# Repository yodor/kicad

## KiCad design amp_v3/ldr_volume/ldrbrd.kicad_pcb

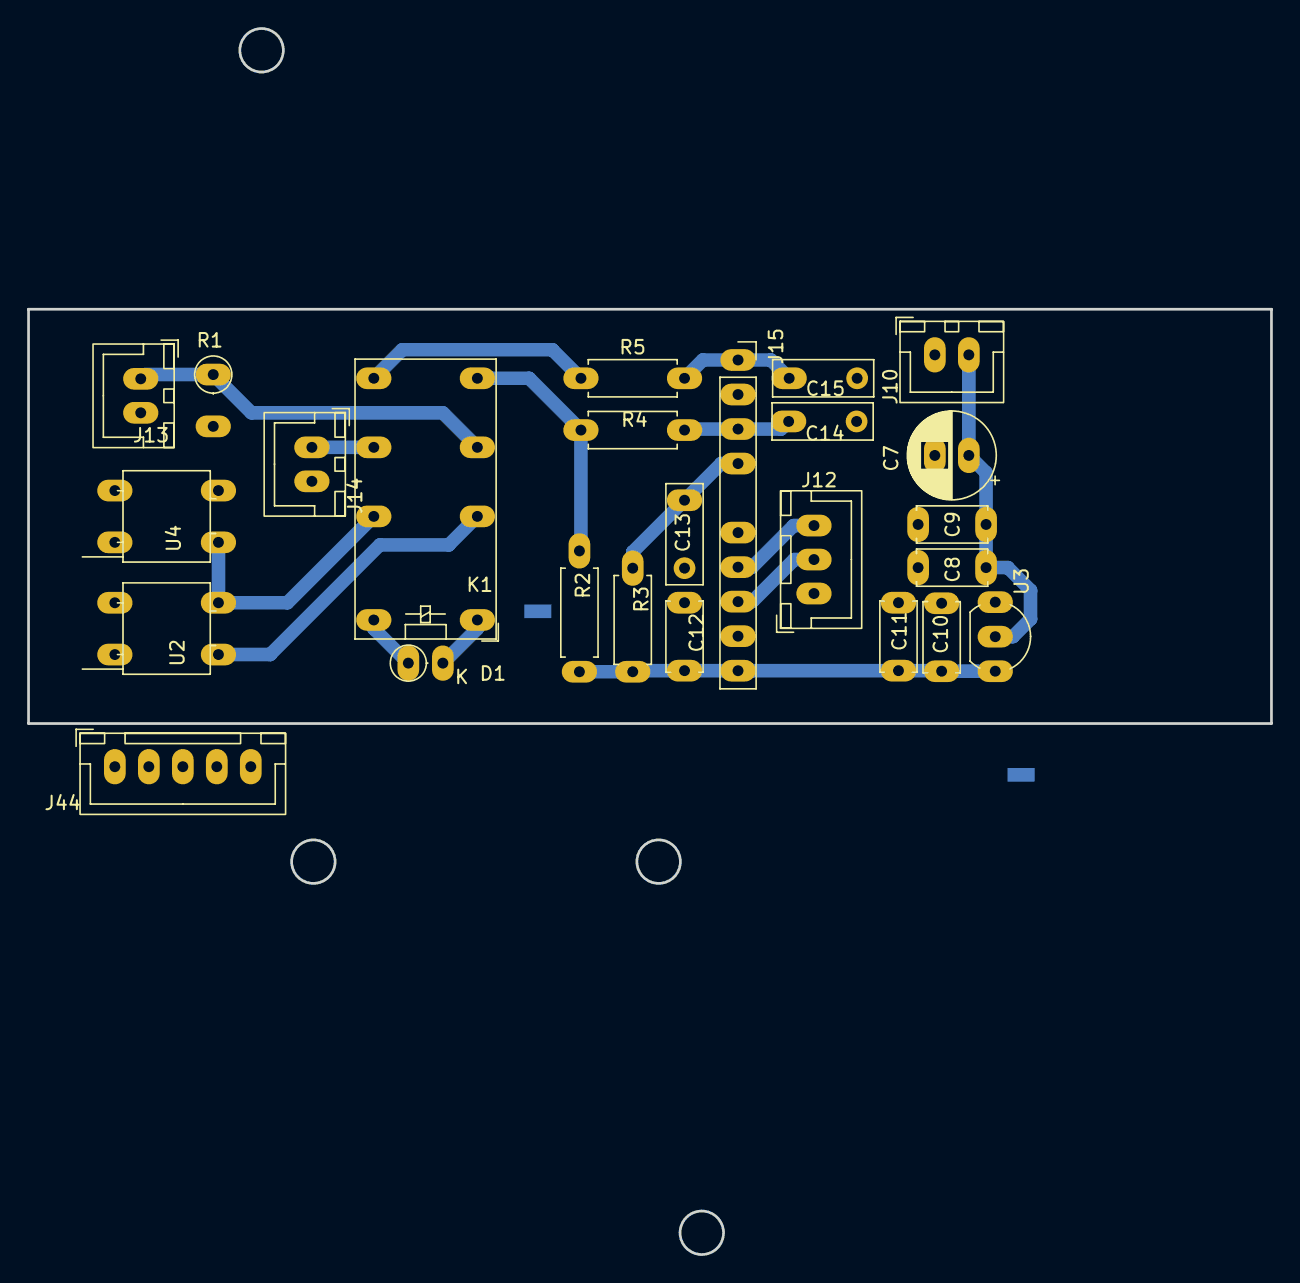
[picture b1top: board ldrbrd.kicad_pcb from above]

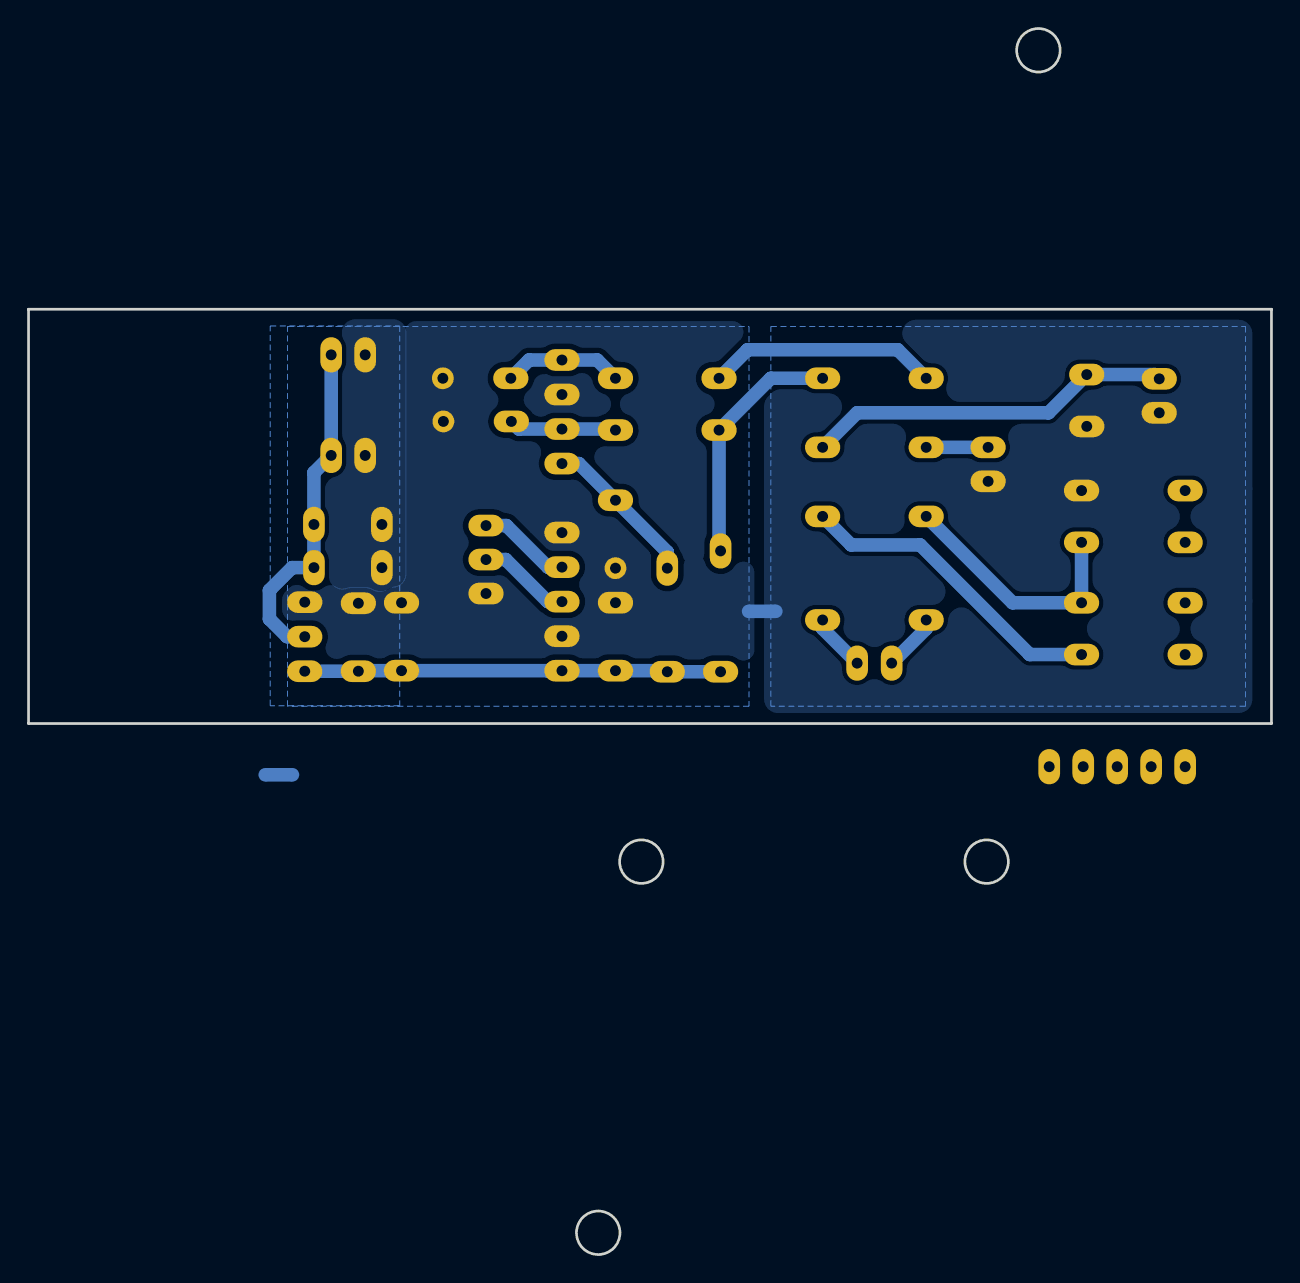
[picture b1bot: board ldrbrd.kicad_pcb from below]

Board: 2 copper layers, 91.4 x 30.5 mm, 27 parts (2 on the bottom side), 21 nets.

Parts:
C7: 100uF; CP_Radial_D6.3mm_P2.50mm
C8, C11: 1uF; C_Disc_D5.0mm_W2.5mm_P5.00mm
C9, C10, C12: 100nF; C_Disc_D5.0mm_W2.5mm_P5.00mm
C13, C14, C15: 100nF; C_Rect_L7.2mm_W2.5mm_P5.00mm_FKS2_FKP2_MKS2_MKP2
D1: 1n4007; D_DO-35_SOD27_P2.54mm_Vertical_CathodeUp
J10: 5v_in; JST_XH_B2B-XH-A_1x02_P2.50mm_Vertical
J12: I2C_R; JST_XH_B3B-XH-A_1x03_P2.50mm_Vertical
J13: A_IN; JST_XH_B2B-XH-A_1x02_P2.50mm_Vertical
J14: A_OUT; JST_XH_B2B-XH-A_1x02_P2.50mm_Vertical
J15: ADS1115; PinSocket_1x10_P2.54mm_Vertical
J44: LDR_L; JST_XH_B5B-XH-A_1x05_P2.50mm_Vertical
K1: G5V-2; Relay_DPDT_Omron_G5V-2
NT1: ATOGNDA; NetTie-2_SMD_Pad1.0o
NT2: AUDIOGND_TO_GNDA; NetTie-2_SMD_Pad1.0o
R1: 1M; R_Axial_DIN0207_L6.3mm_D2.5mm_P2.54mm_Vertical
R2: 10K; R_Axial_DIN0207_L6.3mm_D2.5mm_P7.62mm_Horizontal
R3, R4, R5: 1K; R_Axial_DIN0207_L6.3mm_D2.5mm_P7.62mm_Horizontal
U2: NSL-32-SR3-Rseries; Luna_NSL-32
U3: MCP1700x-330xxTO; TO-92_Inline_Wide
U4: NSL-32-SR3-Rshunt; Luna_NSL-32

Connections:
/LDR Board/5v_ads: C7.1, C8.1, C9.1, J10.2, U3.2 (VI)
/LDR Board/5v_local: D1.1 (K), J44.5, K1.1
/LDR Board/A0: C13.1, J15.4, R3.1
/LDR Board/A1: C14.1, J15.3, R4.1
/LDR Board/A3: C15.1, J15.1, R5.1
/LDR Board/ADS_VDD: C10.1, C11.1, C12.1, J15.10, R2.2, R3.2, U3.3 (VO)
/LDR Board/AUDIO_IN: J13.1, K1.6, R1.1
/LDR Board/AUDIO_OUT: J14.1, K1.11
/LDR Board/COIL_NEG: D1.2 (A), J44.4, K1.16
/LDR Board/MIDDLE_JUNCTION: K1.9, R5.2
/LDR Board/SCL: J12.2, J15.8
/LDR Board/SDA: J12.3, J15.7
/LDR Board/SERIAL_POS: J44.3, U2.1 (A)
/LDR Board/SHUNT_POS: J44.1, U4.1 (A)
/LDR Board/TOP_JUNCTION: K1.8, R2.1, R4.2
/LDR Board/gnd_analog: C7.2, C8.2, C9.2, J10.1, NT1.1
AUDIO_GND: J13.2, J14.2, NT2.1, R1.2, U4.3 (R)
GNDA: C10.2, C11.2, C12.2, C13.2, C14.2, C15.2, J12.1, J15.2, J15.6, J15.9, NT1.2, NT2.2, U3.1 (GND)
GNDD: J44.2, U2.2 (K), U4.2 (K)
unnamed: K1.4, U2.4 (R)
unnamed: K1.13, U2.3 (R), U4.4 (R)

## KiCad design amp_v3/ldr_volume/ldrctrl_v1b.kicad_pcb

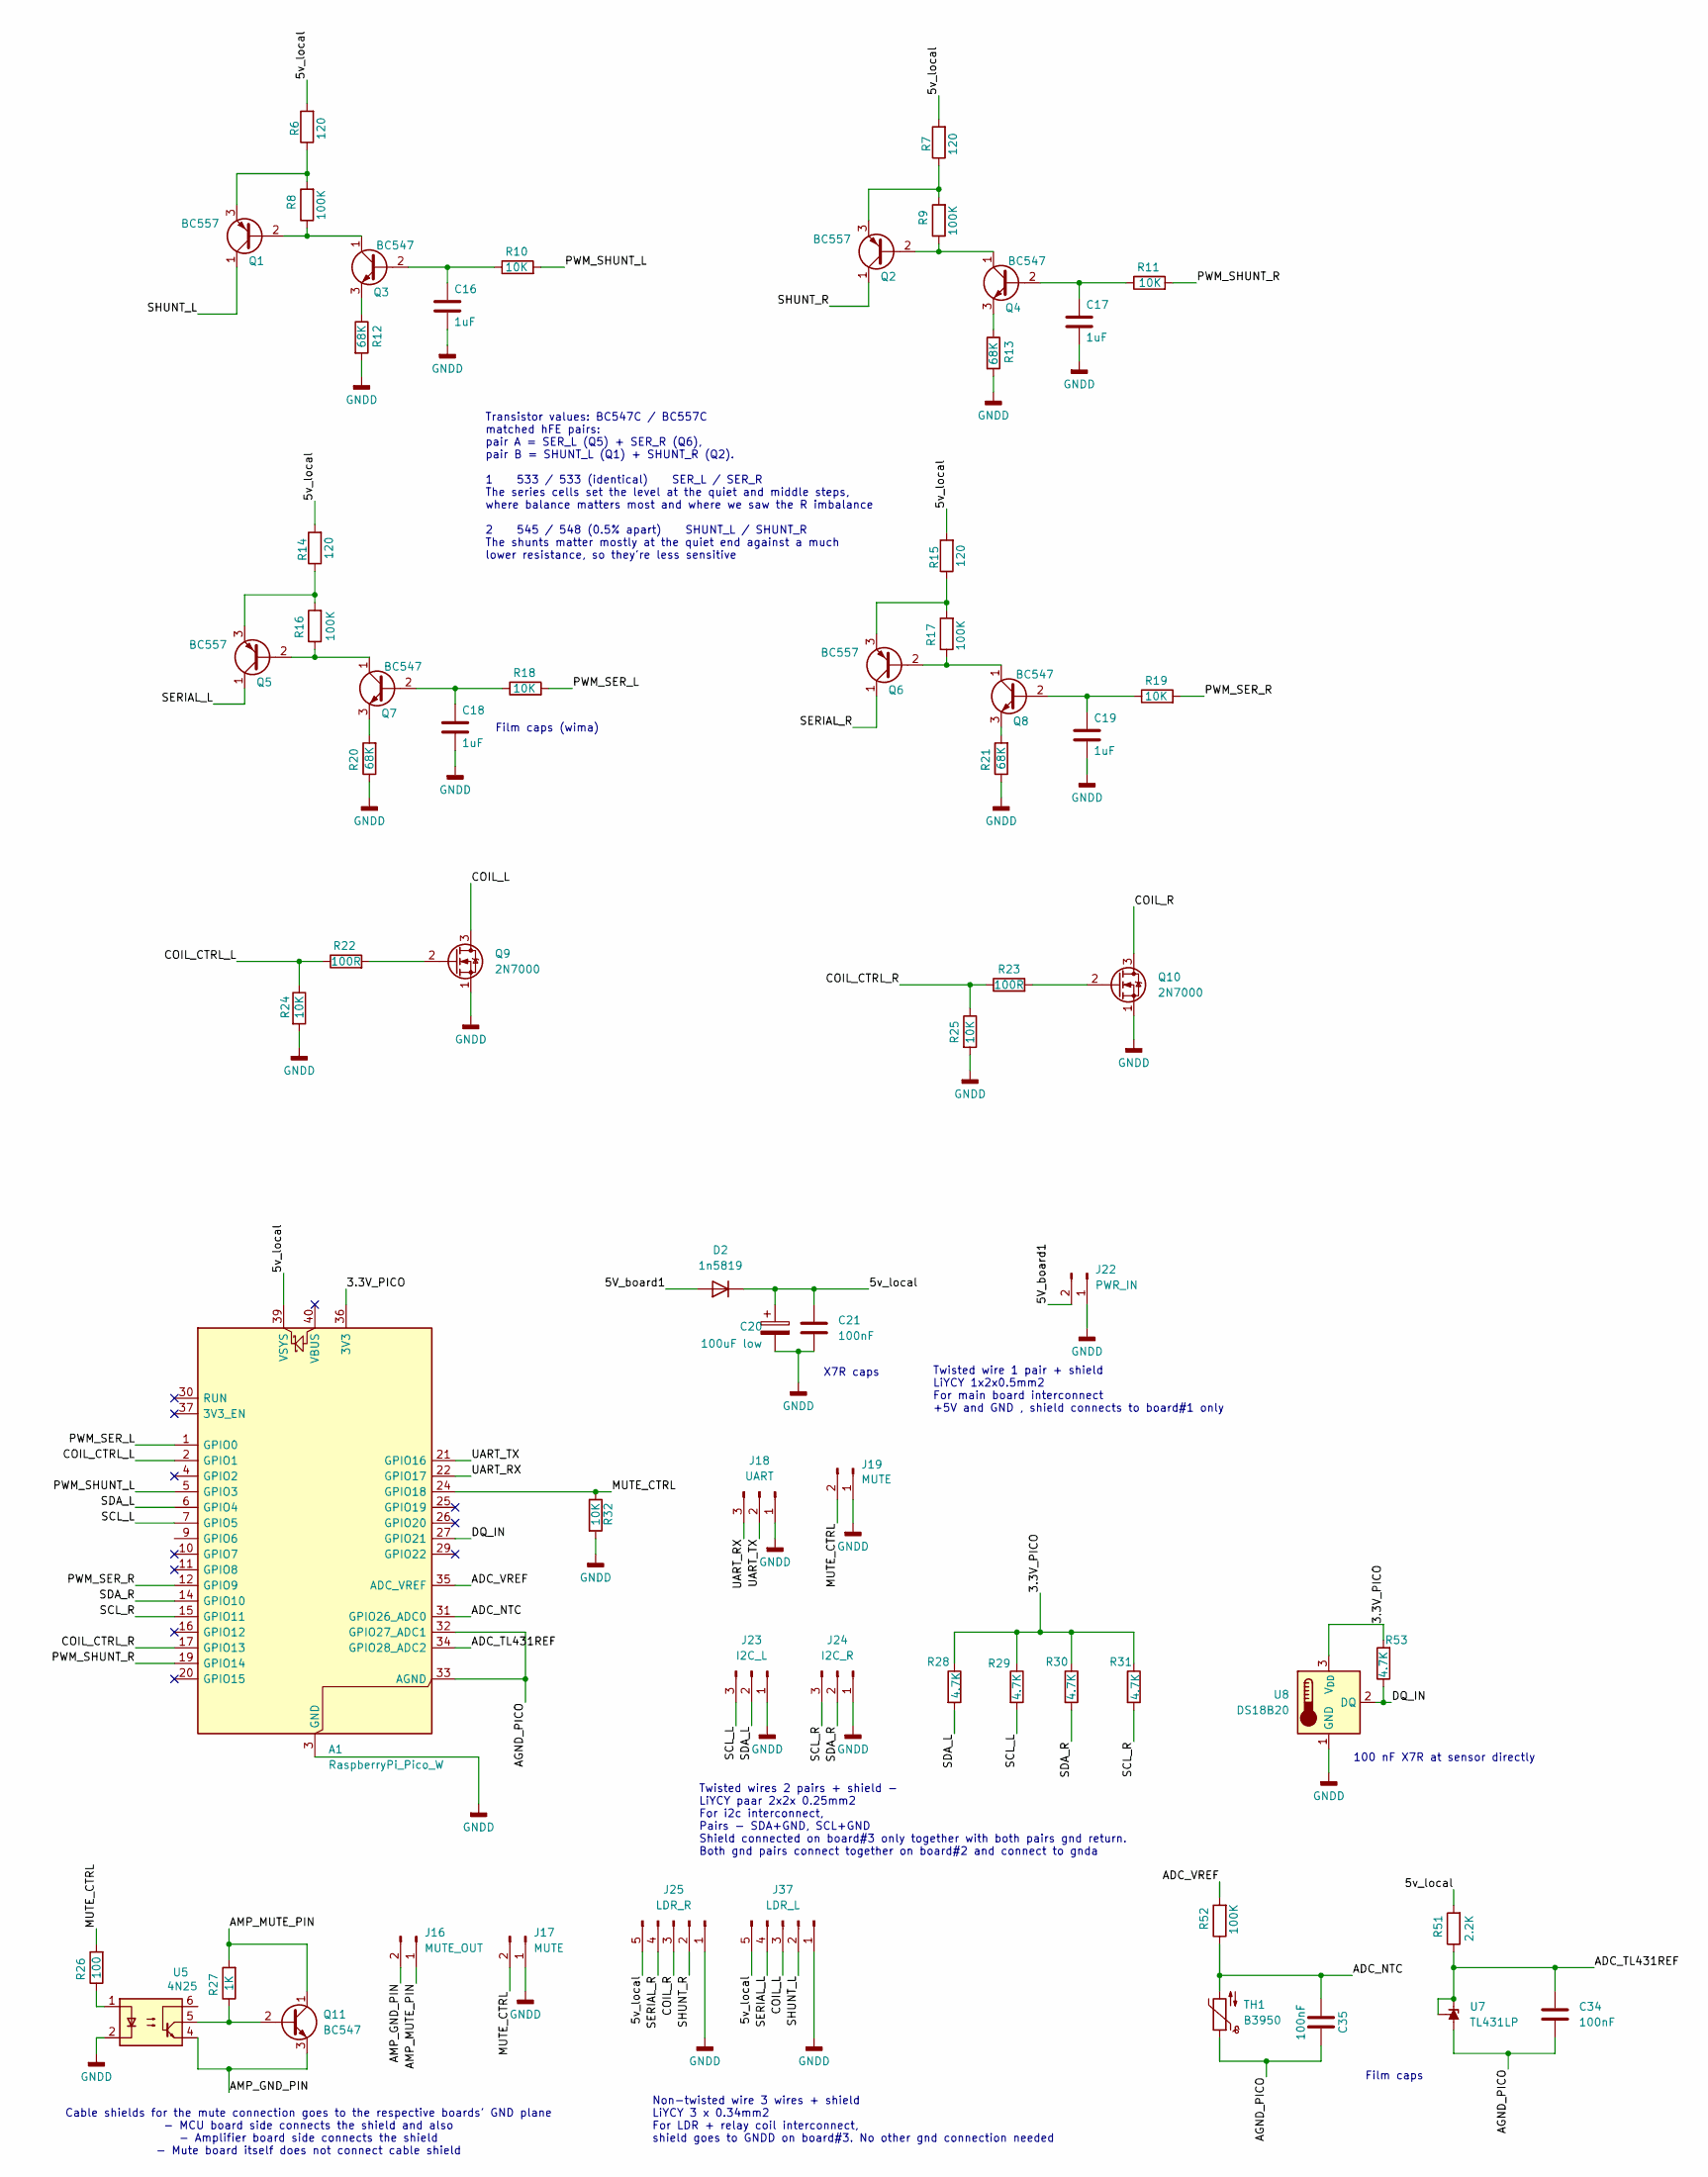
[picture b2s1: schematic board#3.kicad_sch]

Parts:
A1: RaspberryPi_Pico_W; RaspberryPi_Pico_Common_THT
C16, C17, C18, C19: 1uF; C_Rect_L7.2mm_W4.5mm_P5.00mm_FKS2_FKP2_MKS2_MKP2
C20: 100uF low; CP_Radial_D6.3mm_P2.50mm
C21, C34, C35: 100nF; C_Disc_D5.0mm_W2.5mm_P5.00mm
D2: 1n5819; D_DO-41_SOD81_P3.81mm_Vertical_CathodeUp
J16: MUTE_OUT; JST_XH_B2B-XH-A_1x02_P2.50mm_Vertical
J17, J19: MUTE; JST_XH_B2B-XH-A_1x02_P2.50mm_Vertical
J18: UART; JST_XH_B3B-XH-A_1x03_P2.50mm_Vertical
J22: PWR_IN; JST_XH_B2B-XH-A_1x02_P2.50mm_Vertical
J23: I2C_L; JST_XH_B3B-XH-A_1x03_P2.50mm_Vertical
J24: I2C_R; JST_XH_B3B-XH-A_1x03_P2.50mm_Vertical
J25: LDR_R; JST_XH_B5B-XH-A_1x05_P2.50mm_Vertical
J37: LDR_L; JST_XH_B5B-XH-A_1x05_P2.50mm_Vertical
Q1, Q2, Q5, Q6: BC557; TO-92_Inline_Wide
Q3, Q4, Q7, Q8, Q11: BC547; TO-92_Inline_Wide
Q9, Q10: 2N7000; TO-92_Inline_Wide
R6, R7: 120; R_Axial_DIN0207_L6.3mm_D2.5mm_P7.62mm_Horizontal
R8, R9, R16, R17, R52: 100K; R_Axial_DIN0207_L6.3mm_D2.5mm_P7.62mm_Horizontal
R10, R11, R18, R19, R24, R25, R32: 10K; R_Axial_DIN0207_L6.3mm_D2.5mm_P7.62mm_Horizontal
R12, R13, R20, R21: 68K; R_Axial_DIN0207_L6.3mm_D2.5mm_P7.62mm_Horizontal
R14, R15: 120; R_Axial_DIN0207_L6.3mm_D2.5mm_P2.54mm_Vertical
R22, R23: 100R; R_Axial_DIN0207_L6.3mm_D2.5mm_P7.62mm_Horizontal
R26: 100; R_Axial_DIN0207_L6.3mm_D2.5mm_P7.62mm_Horizontal
R27: 1K; R_Axial_DIN0207_L6.3mm_D2.5mm_P7.62mm_Horizontal
R28, R29, R30, R31: 4.7K; R_Axial_DIN0207_L6.3mm_D2.5mm_P7.62mm_Horizontal
R51: 2.2K; R_Axial_DIN0207_L6.3mm_D2.5mm_P7.62mm_Horizontal
R53: 4.7K; R_Axial_DIN0207_L6.3mm_D2.5mm_P2.54mm_Vertical
TH1: B3950; JST_XH_B2B-XH-A_1x02_P2.50mm_Vertical
U5: 4N25; DIP-6_W7.62mm
U7: TL431LP; TO-92_Inline_Wide
U8: DS18B20; JST_XH_B3B-XH-A_1x03_P2.50mm_Vertical

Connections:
/LDR Driver/3.3V_PICO: A1.36 (3V3), R28.1, R29.1, R30.1, R31.1, R53.2, U8.3 (V_{DD})
/LDR Driver/5V_board1: D2.2 (A), J22.2
/LDR Driver/5v_local: A1.39 (VSYS), C20.1, C21.1, D2.1 (K), J25.5, J37.5, R6.2, R7.2, R14.2, R15.2, R51.2
/LDR Driver/ADC_NTC: A1.31 (GPIO26_ADC0), C35.1, R52.1, TH1.2
/LDR Driver/ADC_TL431REF: A1.34 (GPIO28_ADC2), C34.1, R51.1, U7.1 (REF), U7.3 (K)
/LDR Driver/ADC_VREF: A1.35 (ADC_VREF), R52.2
/LDR Driver/AGND_PICO: A1.32 (GPIO27_ADC1), A1.33 (AGND), C34.2, C35.2, TH1.1, U7.2 (A)
/LDR Driver/AMP_GND_PIN: J16.2, Q11.3 (E), U5.4
/LDR Driver/AMP_MUTE_PIN: J16.1, Q11.1 (C), R27.2
/LDR Driver/COIL_CTRL_L: A1.2 (GPIO1), R22.1, R24.1
/LDR Driver/COIL_CTRL_R: A1.17 (GPIO13), R23.1, R25.1
/LDR Driver/COIL_L: J37.3, Q9.3 (D)
/LDR Driver/COIL_R: J25.3, Q10.3 (D)
/LDR Driver/DQ_IN: A1.27 (GPIO21), R53.1, U8.2 (DQ)
/LDR Driver/MUTE_CTRL: A1.24 (GPIO18), J17.2, J19.2, R26.2, R32.1
/LDR Driver/PWM_SER_L: A1.1 (GPIO0), R18.2
/LDR Driver/PWM_SER_R: A1.12 (GPIO9), R19.2
/LDR Driver/PWM_SHUNT_L: A1.5 (GPIO3), R10.2
/LDR Driver/PWM_SHUNT_R: A1.19 (GPIO14), R11.2
/LDR Driver/SCL_L: A1.7 (GPIO5), J23.3, R29.2
/LDR Driver/SCL_R: A1.15 (GPIO11), J24.3, R31.2
/LDR Driver/SDA_L: A1.6 (GPIO4), J23.2, R28.2
/LDR Driver/SDA_R: A1.14 (GPIO10), J24.2, R30.2
/LDR Driver/SERIAL_L: J37.4, Q5.1 (C)
/LDR Driver/SERIAL_R: J25.4, Q6.1 (C)
/LDR Driver/SHUNT_L: J37.2, Q1.1 (C)
/LDR Driver/SHUNT_R: J25.2, Q2.1 (C)
/LDR Driver/UART_RX: A1.22 (GPIO17), J18.3
/LDR Driver/UART_TX: A1.21 (GPIO16), J18.2
GNDD: A1.3 (GND), A1.8 (GND), A1.13 (GND), A1.18 (GND), A1.23 (GND), A1.28 (GND), A1.38 (GND), C16.2, C17.2, C18.2, C19.2, C20.2, C21.2, J17.1, J18.1, J19.1, J22.1, J23.1, J24.1, J25.1, J37.1, Q9.1 (S), Q10.1 (S), R12.2, R13.2, R20.1, R21.1, R24.2, R25.2, R32.2, U5.2, U8.1 (GND)
unnamed: Q1.2 (B), Q3.1 (C), R8.1
unnamed: Q1.3 (E), R6.1, R8.2
unnamed: Q2.2 (B), Q4.1 (C), R9.1
unnamed: Q2.3 (E), R7.1, R9.2
unnamed: C16.1, Q3.2 (B), R10.1
unnamed: Q3.3 (E), R12.1
unnamed: C17.1, Q4.2 (B), R11.1
unnamed: Q4.3 (E), R13.1
unnamed: Q5.2 (B), Q7.1 (C), R16.1
unnamed: Q5.3 (E), R14.1, R16.2
unnamed: Q6.2 (B), Q8.1 (C), R17.1
unnamed: Q6.3 (E), R15.1, R17.2
unnamed: C18.1, Q7.2 (B), R18.1
unnamed: Q7.3 (E), R20.2
unnamed: C19.1, Q8.2 (B), R19.1
unnamed: Q8.3 (E), R21.2
unnamed: Q9.2 (G), R22.2
unnamed: Q10.2 (G), R23.2
unnamed: Q11.2 (B), R27.1, U5.5
unnamed: R26.1, U5.1

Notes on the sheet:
100 nF X7R at sensor directly
Twisted wire 1 pair + shield LiYCY 1x2x0.5mm2 For main board interconnect +5V and GND , shield connects to board#1 only
X7R caps
Film caps
Cable shields for the mute connection goes to the respective boards' GND plane - MCU board side connects the shield and also - Amplifier board side connects the shield - Mute board itself does not connect cable shield
Twisted wires 2 pairs + shield - LiYCY paar 2x2x 0.25mm2 For i2c interconnect, Pairs - SDA+GND, SCL+GND Shield connected on board#3 only together with both pairs gnd return. Both gnd pairs connect together on board#2 and connect to gnda
Transistor values: BC547C / BC557C matched hFE pairs: pair A = SER_L (Q5) + SER_R (Q6), pair B = SHUNT_L (Q1) + SHUNT_R (Q2). 1 533 / 533 (identical) SER_L / SER_R The series cells set the level at the quiet and middle steps, where balance matters most and where we saw the R imbalance 2 545 / 548 (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
Film caps (wima)
Non-twisted wire 3 wires + shield LiYCY 3 x 0.34mm2 For LDR + relay coil interconnect, shield goes to GNDD on board#3. No other gnd connection needed

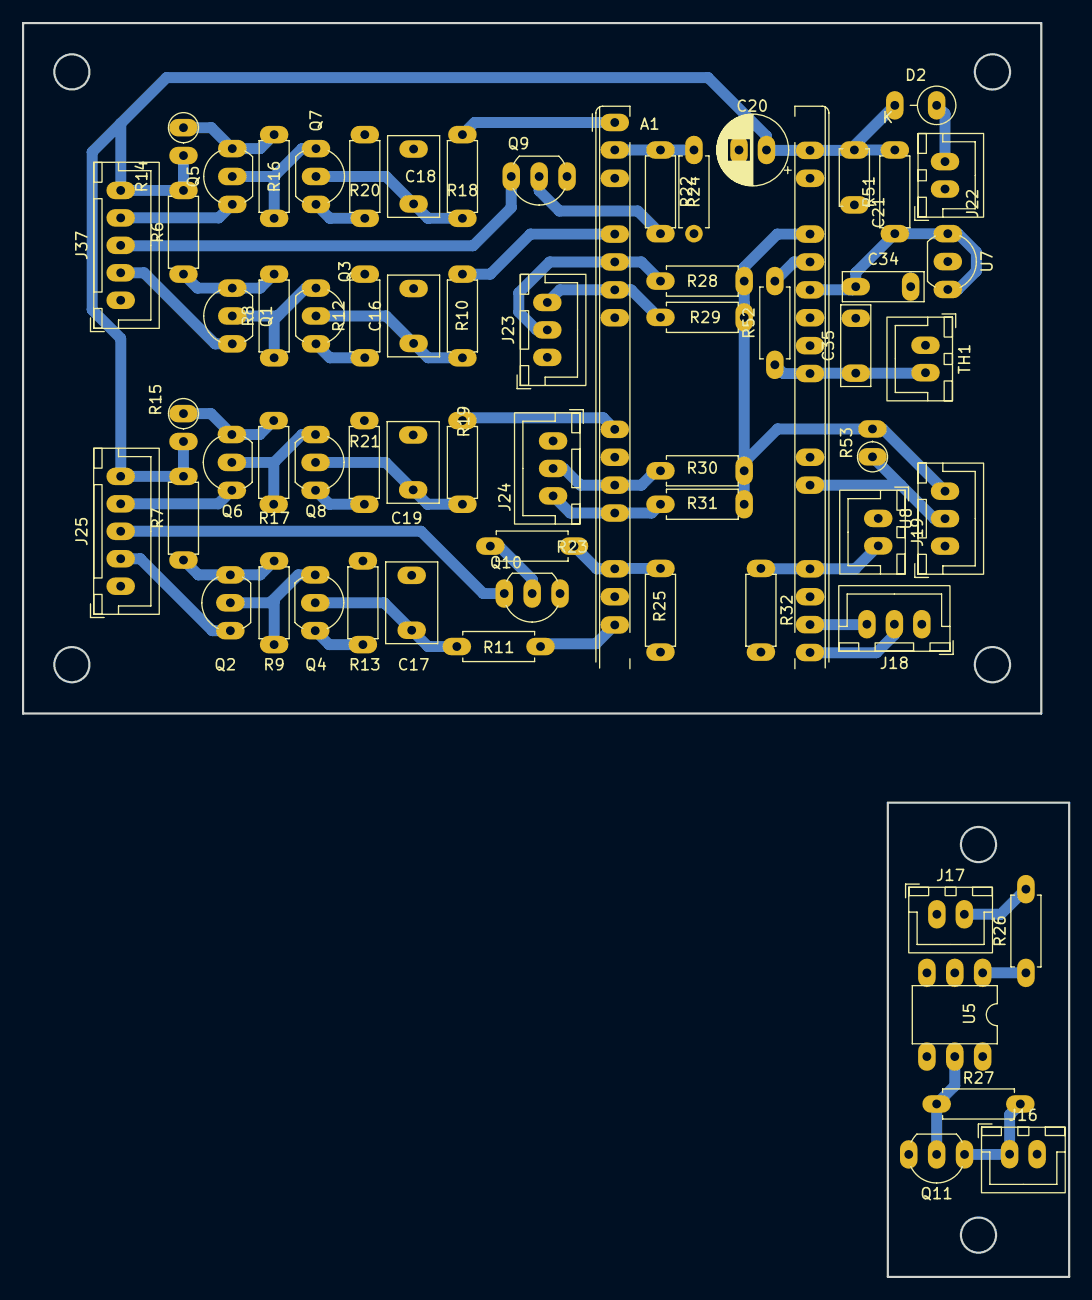
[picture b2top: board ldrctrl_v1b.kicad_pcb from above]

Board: 2 copper layers, 92.7 x 62.9 mm, 64 parts (0 on the bottom side), 50 nets.

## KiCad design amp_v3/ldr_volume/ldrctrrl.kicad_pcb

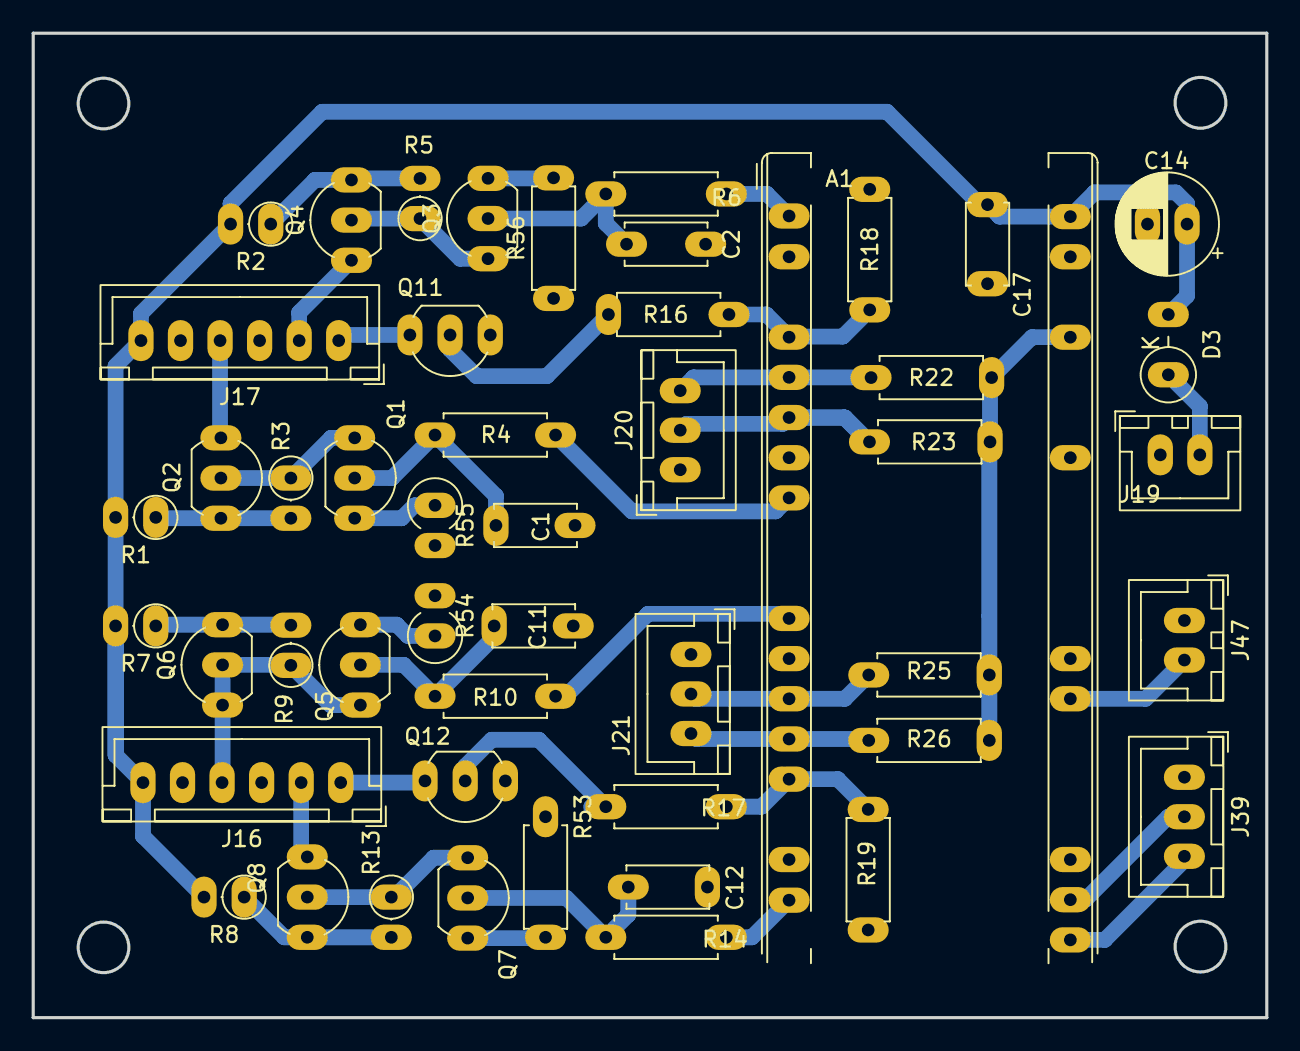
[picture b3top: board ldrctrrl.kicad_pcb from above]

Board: 2 copper layers, 78.0 x 62.2 mm, 49 parts (0 on the bottom side), 41 nets.

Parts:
A1: RaspberryPi_Pico_W; RaspberryPi_Pico_Common_THT
C1, C2, C11, C12: 10nF; C_Disc_D5.0mm_W2.5mm_P5.00mm
C14: 100uF low; CP_Radial_D6.3mm_P2.50mm
C17: 100nF; C_Disc_D5.0mm_W2.5mm_P5.00mm
D3: 1n5819; D_DO-41_SOD81_P3.81mm_Vertical_CathodeUp
J16, J17: CTRL; JST_XH_B6B-XH-A_1x06_P2.50mm_Vertical
J19: PWR_IN; JST_XH_B2B-XH-A_1x02_P2.50mm_Vertical
J20: I2C_L; JST_XH_B3B-XH-A_1x03_P2.50mm_Vertical
J21: I2C_R; JST_XH_B3B-XH-A_1x03_P2.50mm_Vertical
J39: UART; JST_XH_B3B-XH-A_1x03_P2.50mm_Vertical
J47: MUTE; JST_XH_B2B-XH-A_1x02_P2.50mm_Vertical
Q1, Q3, Q5, Q7: BC547; TO-92_Inline_Wide
Q2, Q4, Q6, Q8: BC557; TO-92_Inline_Wide
Q11, Q12: 2N7000; TO-92_Inline_Wide
R1, R2, R7, R8: 120; R_Axial_DIN0207_L6.3mm_D2.5mm_P2.54mm_Vertical
R3, R5, R9, R13: 100K; R_Axial_DIN0207_L6.3mm_D2.5mm_P2.54mm_Vertical
R4, R6, R10, R14, R18, R19: 10K; R_Axial_DIN0207_L6.3mm_D2.5mm_P7.62mm_Horizontal
R16, R17: 100R; R_Axial_DIN0207_L6.3mm_D2.5mm_P7.62mm_Horizontal
R22, R23, R25, R26: 4.7K; R_Axial_DIN0207_L6.3mm_D2.5mm_P7.62mm_Horizontal
R53, R56: 68K; R_Axial_DIN0207_L6.3mm_D2.5mm_P7.62mm_Horizontal
R54, R55: 68K; R_Axial_DIN0309_L9.0mm_D3.2mm_P2.54mm_Vertical

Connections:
/LDR Driver/3.3V_PICO: A1.36 (3V3), R22.1, R23.1, R25.1, R26.1
/LDR Driver/5V_board1: D3.2 (A), J19.2
/LDR Driver/5v_local: A1.39 (VSYS), C14.1, C17.1, D3.1 (K), J16.6, J17.6, R1.2, R2.2, R7.2, R8.2
/LDR Driver/COIL_CTRL_L: A1.5 (GPIO3), R16.1, R18.1
/LDR Driver/COIL_CTRL_R: A1.16 (GPIO12), R17.1, R19.1
/LDR Driver/COIL_L: J17.1, Q11.3 (D)
/LDR Driver/COIL_R: J16.1, Q12.3 (D)
/LDR Driver/MUTE_CTRL: A1.27 (GPIO21), J47.2
/LDR Driver/PWM_SER_L: A1.2 (GPIO1), R6.2
/LDR Driver/PWM_SER_R: A1.19 (GPIO14), R14.2
/LDR Driver/PWM_SHUNT_L: A1.9 (GPIO6), R4.2
/LDR Driver/PWM_SHUNT_R: A1.12 (GPIO9), R10.2
/LDR Driver/SCL_L: A1.7 (GPIO5), J20.2, R23.2
/LDR Driver/SCL_R: A1.15 (GPIO11), J21.3, R26.2
/LDR Driver/SDA_L: A1.6 (GPIO4), J20.3, R22.2
/LDR Driver/SDA_R: A1.14 (GPIO10), J21.2, R25.2
/LDR Driver/SERIAL_L: J17.2, Q4.1 (C)
/LDR Driver/SERIAL_R: J16.2, Q8.1 (C)
/LDR Driver/SHUNT_L: J17.4, Q2.1 (C)
/LDR Driver/SHUNT_R: J16.4, Q6.1 (C)
/LDR Driver/UART_RX: A1.21 (GPIO16), J39.3
/LDR Driver/UART_TX: A1.22 (GPIO17), J39.2
GNDD: A1.3 (GND), A1.8 (GND), A1.13 (GND), A1.18 (GND), A1.23 (GND), A1.28 (GND), A1.33 (AGND), A1.38 (GND), C1.2, C2.2, C11.2, C12.2, C14.2, C17.2, J16.3, J16.5, J17.3, J17.5, J19.1, J20.1, J21.1, J39.1, J47.1, Q11.1 (S), Q12.1 (S), R18.2, R19.2, R53.1, R54.2, R55.2, R56.1
unnamed: C1.1, Q1.2 (B), R4.1
unnamed: Q1.1 (C), Q2.2 (B), R3.1
unnamed: Q1.3 (E), R55.1
unnamed: Q2.3 (E), R1.1, R3.2
unnamed: C2.1, Q3.2 (B), R6.1
unnamed: Q3.1 (C), Q4.2 (B), R5.1
unnamed: Q3.3 (E), R56.2
unnamed: Q4.3 (E), R2.1, R5.2
unnamed: C11.1, Q5.2 (B), R10.1
unnamed: Q5.1 (C), Q6.2 (B), R9.1
unnamed: Q5.3 (E), R54.1
unnamed: Q6.3 (E), R7.1, R9.2
unnamed: C12.1, Q7.2 (B), R14.1
unnamed: Q7.1 (C), Q8.2 (B), R13.1
unnamed: Q7.3 (E), R53.2
unnamed: Q8.3 (E), R8.1, R13.2
unnamed: Q11.2 (G), R16.2
unnamed: Q12.2 (G), R17.2

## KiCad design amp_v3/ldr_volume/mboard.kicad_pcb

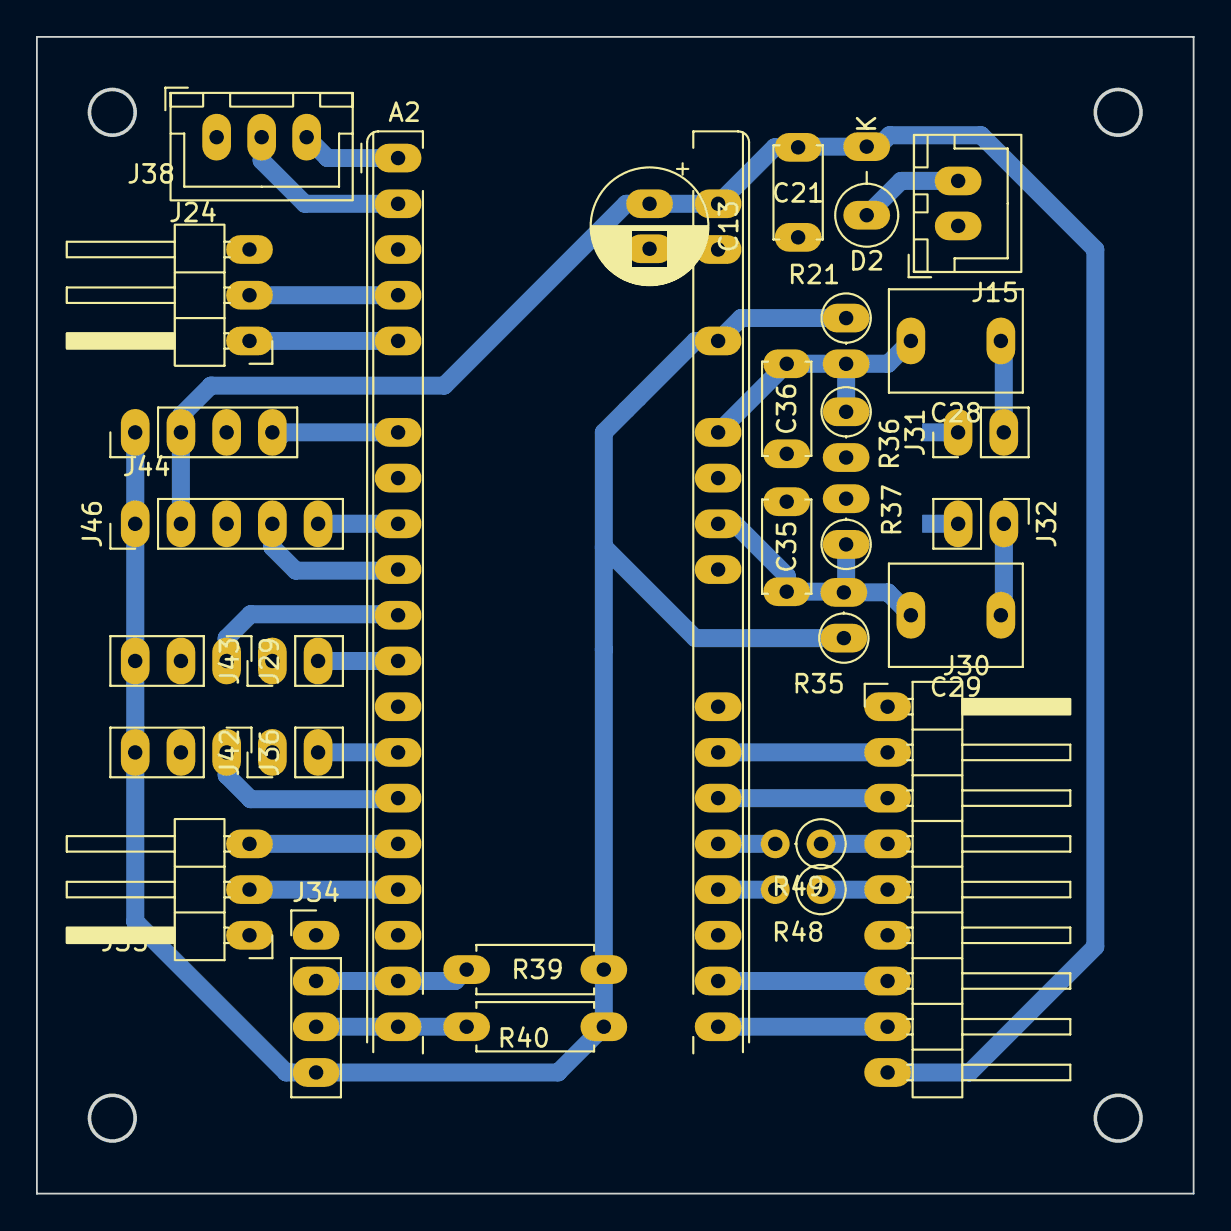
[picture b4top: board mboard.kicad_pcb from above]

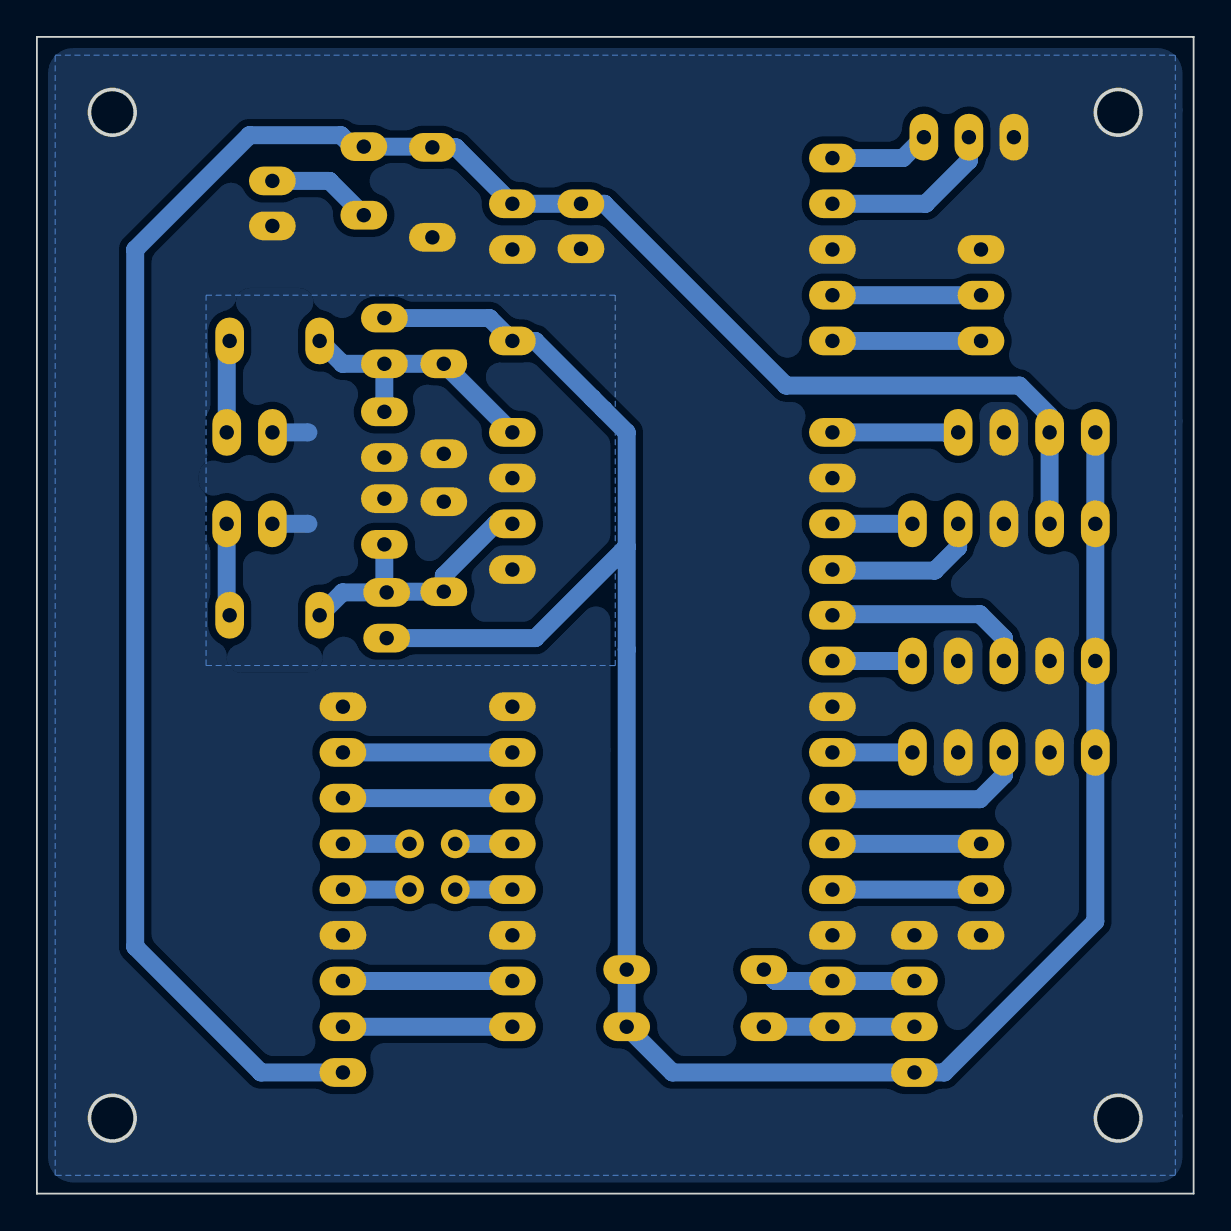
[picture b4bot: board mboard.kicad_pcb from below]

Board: 2 copper layers, 64.3 x 64.3 mm, 32 parts (2 on the bottom side), 34 nets.

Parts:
A2: RaspberryPi_Pico_W; RaspberryPi_Pico_Common_THT
C13: 100uF low; CP_Radial_D6.3mm_P2.50mm
C21: 100nF; C_Disc_D5.0mm_W2.5mm_P5.00mm
C28, C29: 1uF; C_Rect_L7.2mm_W5.5mm_P5.00mm_FKS2_FKP2_MKS2_MKP2
C35, C36: 10nF; C_Disc_D5.0mm_W2.5mm_P5.00mm
D2: 1n5817; D_DO-41_SOD81_P3.81mm_Vertical_CathodeUp
J15: PWR_IN; JST_XH_B2B-XH-A_1x02_P2.50mm_Vertical
J24: UART; JST_XH_B3B-XH-A_1x03_P2.50mm_Vertical
J29: IR; PinHeader_1x03_P2.54mm_Vertical
J30: TFT; PinHeader_1x09_P2.54mm_Horizontal
J31: S_AIN_L; PinHeader_1x02_P2.54mm_Vertical
J32: S_AIN_R; PinHeader_1x02_P2.54mm_Vertical
J34: I2C; PinHeader_1x04_P2.54mm_Vertical
J35: BTN_VOL; PinHeader_1x03_P2.54mm_Horizontal
J36: MUTE; PinHeader_1x03_P2.54mm_Vertical
J38: BTN_MENU; PinHeader_1x03_P2.54mm_Horizontal
J42: PWR_BTN; PinHeader_1x02_P2.54mm_Vertical
J43: PWR_BTN_LED; PinHeader_1x02_P2.54mm_Vertical
J44: PWR_RLY; PinHeader_1x04_P2.54mm_Vertical
J46: ALPS; PinHeader_1x05_P2.54mm_Vertical
NT7, NT8: NetTie_2; NetTie-2_SMD_Pad1.0o
R21, R35, R36, R37: 10K; R_Axial_DIN0207_L6.3mm_D2.5mm_P2.54mm_Vertical
R39, R40: 4.7K; R_Axial_DIN0207_L6.3mm_D2.5mm_P7.62mm_Horizontal
R48, R49: 22; R_Axial_DIN0207_L6.3mm_D2.5mm_P2.54mm_Vertical

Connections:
/board#5/3.3V_PICO: A2.36 (3V3), J29.3, J34.4, J36.3, J44.1, J46.1, R21.1, R35.1, R39.1, R40.1
/board#5/5V_board1: D2.2 (A), J15.2
/board#5/5v_local: A2.39 (VSYS), C13.1, C21.1, D2.1 (K), J30.9, J44.2, J46.2
/board#5/ADC_L: A2.34 (GPIO28_ADC2), C28.2, C36.1, R21.2, R36.1
/board#5/ADC_R: A2.32 (GPIO27_ADC1), C29.2, C35.2, R35.2, R37.1
/board#5/AGND_L: J31.1, NT8.1
/board#5/AGND_PICO: A2.31 (GPIO26_ADC0), A2.33 (AGND), C35.1, C36.2, NT7.2, NT8.2, R36.2, R37.2
/board#5/AGND_R: J32.2, NT7.1
/board#5/ALPS_L: A2.10 (GPIO7), J46.4
/board#5/ALPS_R: A2.9 (GPIO6), J46.5
/board#5/AUDIO_L: C28.1, J31.2
/board#5/AUDIO_R: C29.1, J32.1
/board#5/BTN_DN: A2.17 (GPIO13), J35.2
/board#5/BTN_LT: A2.16 (GPIO12), J35.3
/board#5/BTN_RT: A2.5 (GPIO3), J38.1
/board#5/BTN_UP: A2.4 (GPIO2), J38.2
/board#5/IR: A2.11 (GPIO8), J29.1
/board#5/MUTE_CTRL: A2.15 (GPIO11), J36.1
/board#5/PWR_BTN: A2.14 (GPIO10), J42.2
/board#5/PWR_BTN_LED: A2.12 (GPIO9), J43.2
/board#5/RLCTRL: A2.7 (GPIO5), J44.4
/board#5/SCL: A2.20 (GPIO15), J34.3, R40.2
/board#5/SDA: A2.19 (GPIO14), J34.2, R39.2
/board#5/TFT_BLK: A2.27 (GPIO21), J30.2
/board#5/TFT_CS: A2.22 (GPIO17), J30.7
/board#5/TFT_DC: A2.21 (GPIO16), J30.8
/board#5/TFT_RST: A2.26 (GPIO20), J30.3
/board#5/TFT_SCL: J30.5, R48.1
/board#5/TFT_SDA: J30.4, R49.1
/board#5/UART_RX: A2.2 (GPIO1), J24.2
/board#5/UART_TX: A2.1 (GPIO0), J24.3
GNDD: A2.3 (GND), A2.8 (GND), A2.13 (GND), A2.18 (GND), A2.23 (GND), A2.28 (GND), A2.38 (GND), C13.2, C21.2, J15.1, J24.1, J29.2, J30.1, J30.6, J34.1, J35.1, J36.2, J38.3, J42.1, J43.1, J44.3, J46.3
unnamed: A2.24 (GPIO18), R48.2
unnamed: A2.25 (GPIO19), R49.2

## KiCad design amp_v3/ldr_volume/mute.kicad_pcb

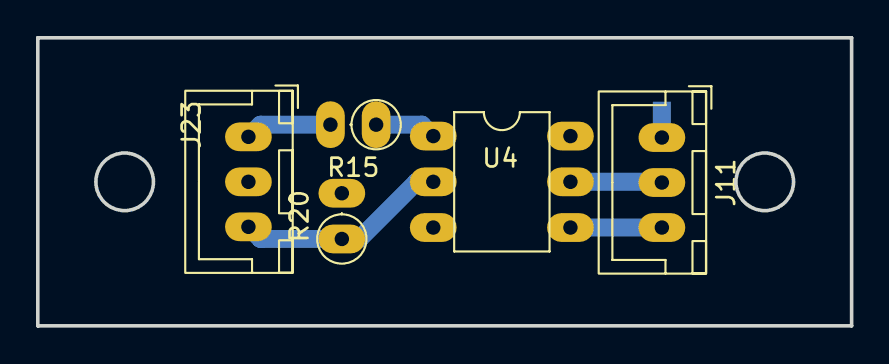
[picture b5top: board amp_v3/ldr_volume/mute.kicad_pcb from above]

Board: 2 copper layers, 45.2 x 16.0 mm, 6 parts (1 on the bottom side), 7 nets.

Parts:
J11, J23: MUTE; JST_XH_B3B-XH-A_1x03_P2.50mm_Vertical
NT3: mute_cable; NetTie-2_SMD_Pad1.0o
R15: 300; R_Axial_DIN0207_L6.3mm_D2.5mm_P2.54mm_Vertical
R20: 1K; R_Axial_DIN0207_L6.3mm_D2.5mm_P2.54mm_Vertical
U4: 4N25; DIP-6_W7.62mm

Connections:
/board#3/3.3V_PICO: J23.1, R15.2
/board#3/AMP_GND_PIN: J11.3, U4.4
/board#3/AMP_MUTE_PIN: J11.2, U4.5
/board#3/CABLE_SHD: J11.1, NT3.1
/board#3/MUTE_CTRL: J23.3, R20.1, U4.2
GNDD: J23.2, NT3.2, R20.2
unnamed: R15.1, U4.1
